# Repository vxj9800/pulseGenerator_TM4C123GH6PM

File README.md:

# pulseGenerator_TM4C123GH6PM
Design and code for a low cost system capable of generating various waveforms on two analog outputs while also providing two analog inputs to measure the amplitude of a signal.

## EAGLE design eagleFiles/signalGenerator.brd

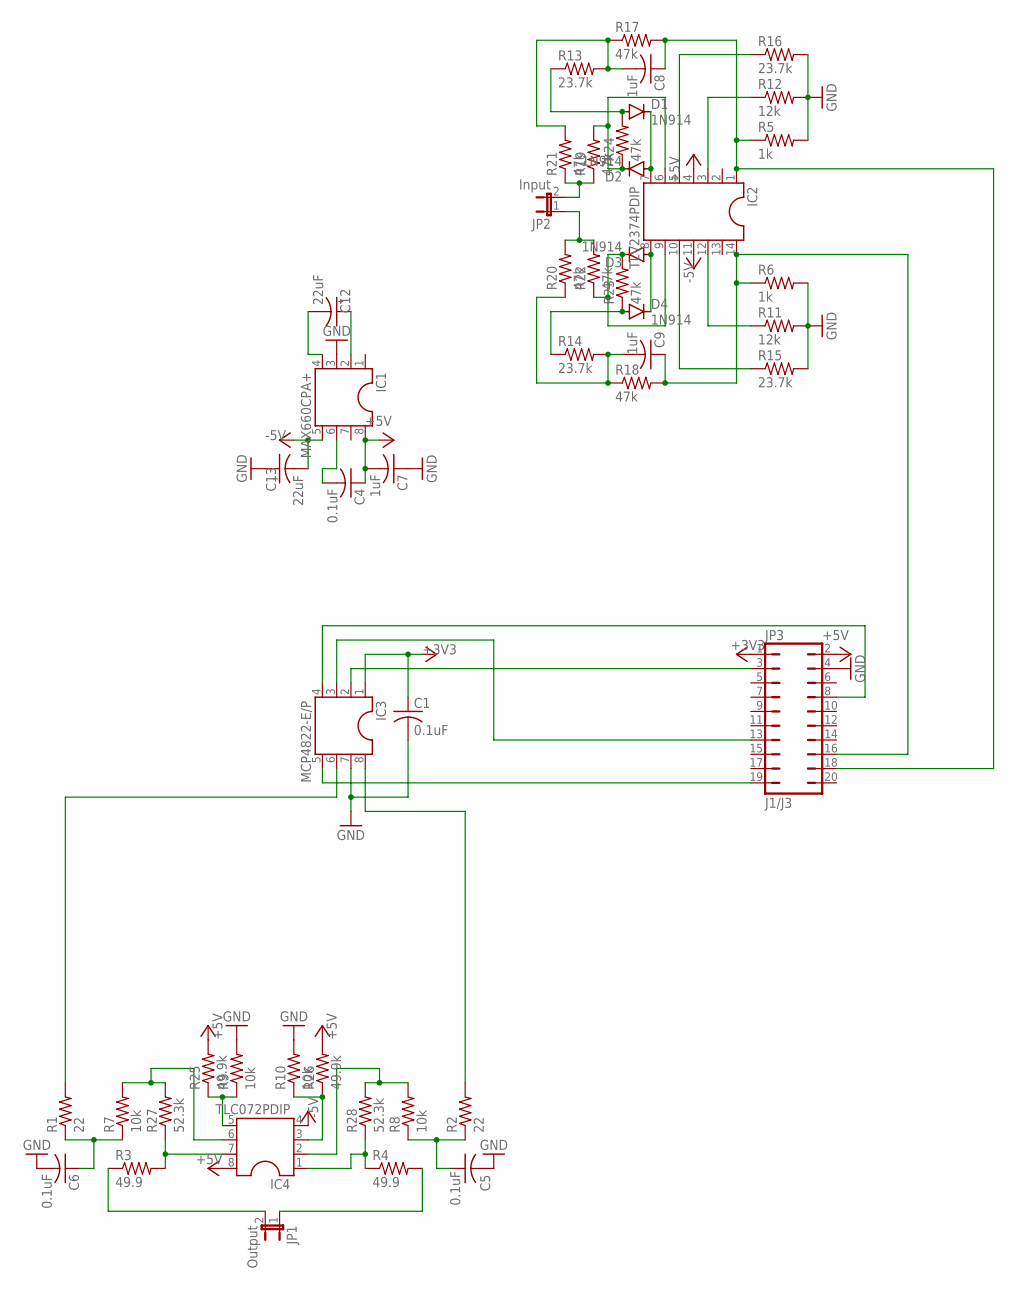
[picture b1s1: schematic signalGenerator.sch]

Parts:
C1, C4, C5, C6: 0.1uF; C050-025X075
C7, C8, C9: 1uF; C050-025X075
C12, C13: 22uF; E5-4
D1, D2, D3, D4: 1N914; DO35-7
IC1: MAX660CPA+; SOCKET-08
IC2: TLV2374PDIP; SOCKET-14
IC3: MCP4822-E/P; SOCKET-08
IC4: TLC072PDIP; SOCKET-08
JP1: Output; JP1
JP2: Input; JP1
JP3: J1/J3; JP10Q
R1, R2: 22; 0207/10
R3, R4: 49.9; 0207/10
R5, R6: 1k; 0207/10
R7, R8, R9, R10: 10k; 0207/10
R11, R12: 12k; 0207/10
R13, R14, R15, R16: 23.7k; 0207/10
R17, R18, R19, R20, R21, R22, R23, R24: 47k; 0207/10
R25, R26: 49.9k; 0207/10
R27, R28: 52.3k; 0207/10

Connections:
+3V3: C1.1, IC3.1, JP3.1
+5V: C4.1, C7.2, IC1.8, IC2.4, IC4.8, JP3.2, R25.2, R26.2
-5V: C13.-, IC1.5, IC2.11, IC4.4
GND: C1.2, C5.2, C6.2, C7.1, C13.+, IC1.3, IC3.7, JP3.4, R5.2, R6.2, R9.2, R10.2, R11.2, R12.2, R15.2, R16.2
unnamed: IC4.3, R10.1, R26.1
unnamed: IC3.2, JP3.3
unnamed: IC3.3, JP3.13
unnamed: IC3.4, JP3.8
unnamed: IC3.5, JP3.19
unnamed: IC3.6, R1.2
unnamed: IC3.8, R2.2
unnamed: IC4.6, R7.2, R27.2
unnamed: IC4.2, R8.2, R28.2
unnamed: C6.1, R1.1, R7.1
unnamed: C5.1, R2.1, R8.1
unnamed: JP1.2, R3.1
unnamed: JP1.1, R4.2
unnamed: IC4.7, R3.2, R27.1
unnamed: IC4.1, R4.1, R28.1
unnamed: IC4.5, R9.1, R25.1
unnamed: C12.-, IC1.4
unnamed: C4.2, IC1.6
unnamed: C12.+, IC1.2
unnamed: C8.2, R13.2, R17.1, R21.2
unnamed: C9.2, R14.2, R18.1, R20.1
unnamed: IC2.3, R12.1
unnamed: IC2.12, R11.1
unnamed: IC2.5, R16.1
unnamed: IC2.10, R15.1
unnamed: C8.1, IC2.1, JP3.18, R5.1, R17.2
unnamed: C9.1, IC2.14, JP3.16, R6.1, R18.2
unnamed: D1.C, D2.A, IC2.7
unnamed: D3.A, D4.C, IC2.8
unnamed: D2.C, IC2.6, R19.2, R24.1
unnamed: D1.A, R13.1, R24.2
unnamed: D3.C, IC2.9, R22.1, R23.2
unnamed: D4.A, R14.1, R23.1
unnamed: JP2.2, R19.1, R21.1
unnamed: JP2.1, R20.2, R22.2

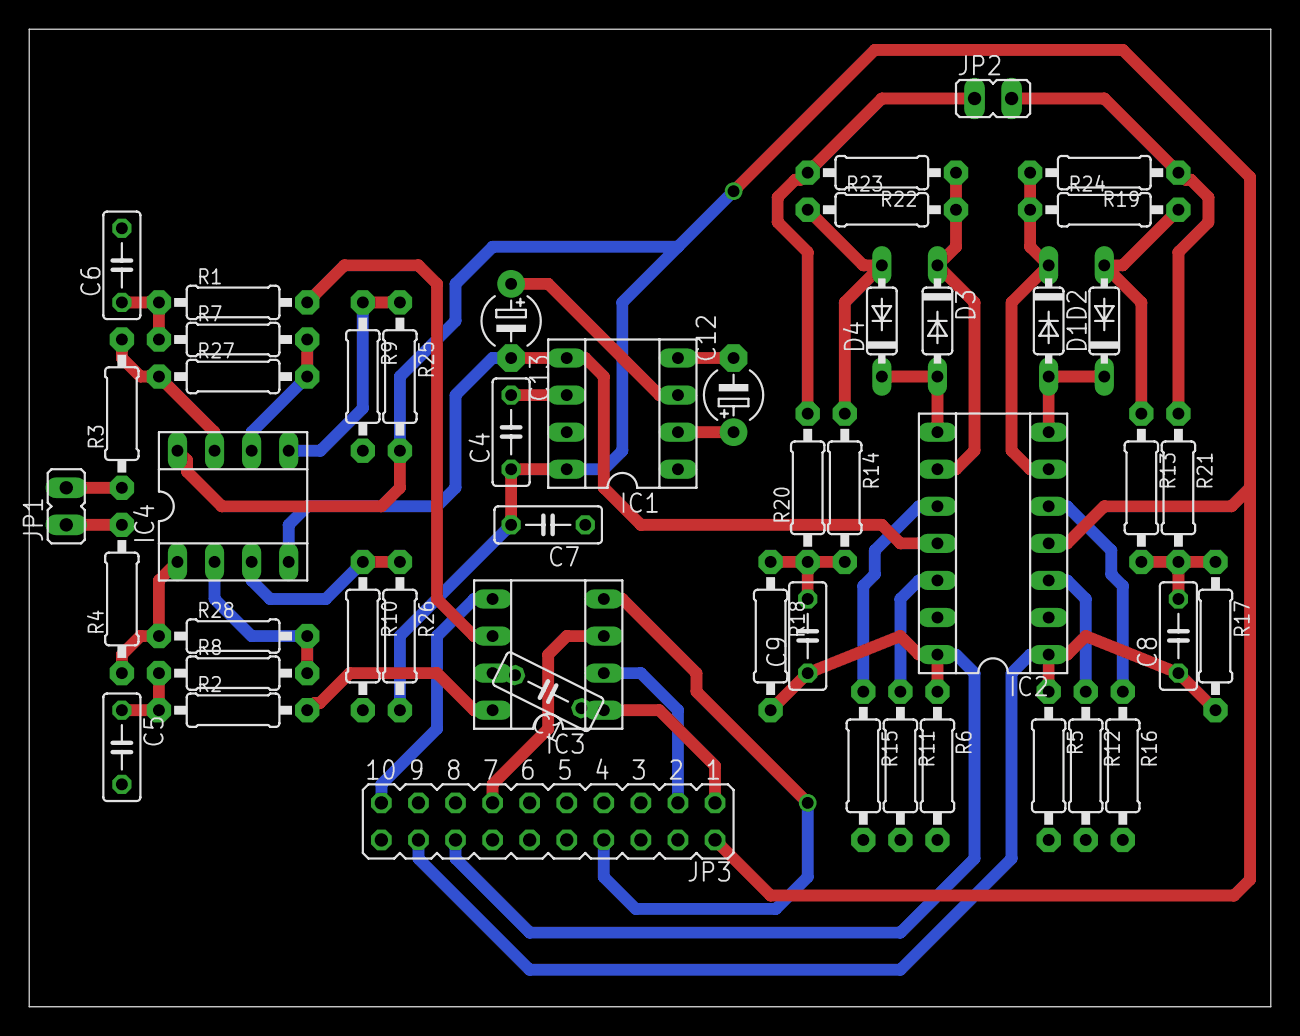
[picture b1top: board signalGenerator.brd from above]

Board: 2 copper layers, 85.1 x 67.0 mm, 48 parts (0 on the bottom side), 39 nets.

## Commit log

2021-07-31 Add circuit schematic
2021-07-31 Add code
